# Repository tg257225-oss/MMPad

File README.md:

# MMPad
This is my first macro pad. Its a simple 3x3 grid of switches, with a rotary encoder and OLED display (which will likely be Jolteon). This project was really fun (and frustrating) to make, but I did learn a lot and hope to make an even better one in the future!
# PCB/Schematic
The PCB and Schematic were designed in Kicad.

# CAD
The case and plate were designed in Fusion360. 

## BOM
- 1x 0.96" OLED Screen - $3.90 on SeeedStudio
- 1x EC11 Rotary Encoder - $1.99 on Keebio
- 9x MX Switches - $0.99 on AliExpress (10-count Cherry MX Brown Switches)
- 10x 1N4148 Diodes - $2.99 on Keebio 
- 1x Seeed XIAO RP2040 $3.99 on SeeedStudio
- 9x DSA Keycaps - $0.99 on AliExpress (10-count DSA 1U Black Keycaps)
- 4x M3x16mm screws - $8.99 on Amazon
### Total is $23.84

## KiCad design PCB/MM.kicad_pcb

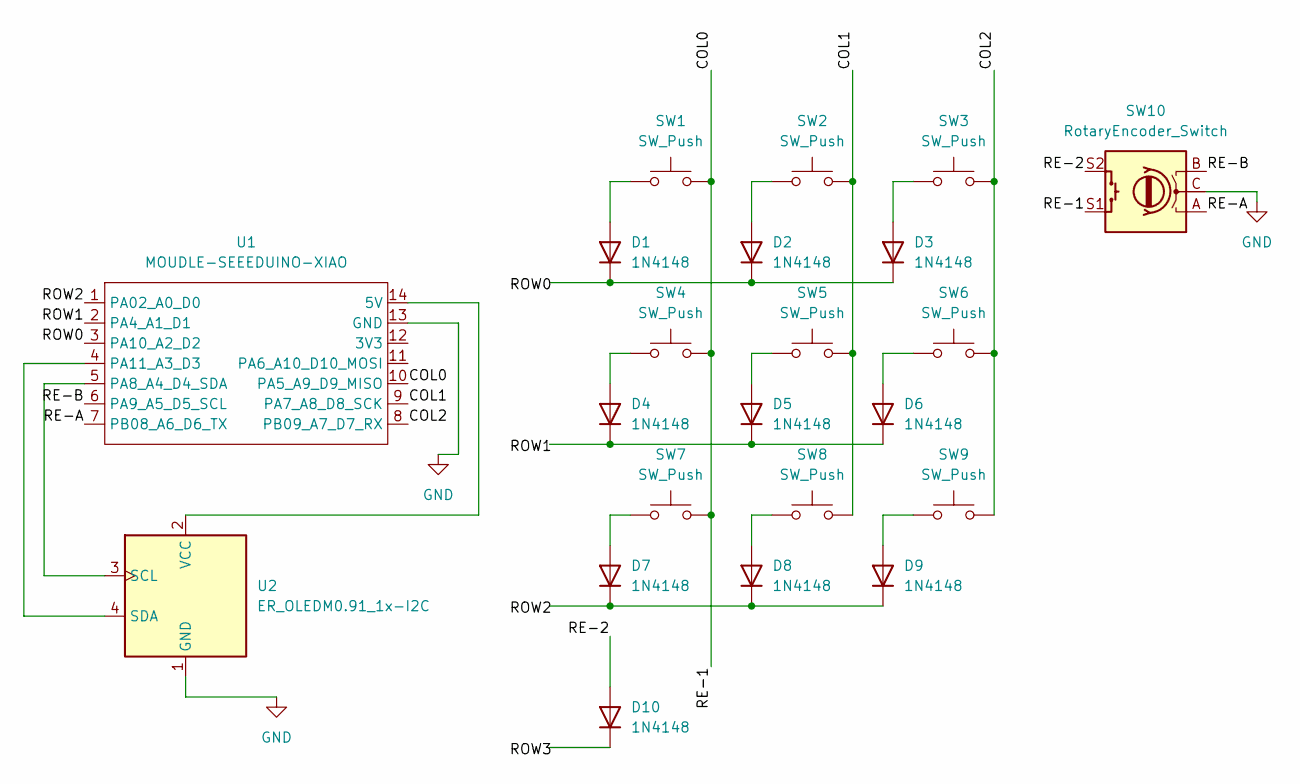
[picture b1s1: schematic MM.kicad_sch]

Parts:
D1, D2, D3, D4, D5, D6, D7, D8, D9, D10: 1N4148; D_DO-35_SOD27_P7.62mm_Horizontal
SW1, SW2, SW3, SW4, SW5, SW6, SW7, SW8, SW9: SW_Push; SW_Cherry_MX_1.00u_PCB
SW10: RotaryEncoder_Switch; RotaryEncoder_Alps_EC11E-Switch_Vertical_H20mm
U1: MOUDLE-SEEEDUINO-XIAO; XIAO-Generic-Hybrid-14P-2.54-21X17.8MM
U2: ER_OLEDM0.91_1x-I2C

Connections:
/COL0: SW1.2, SW4.2, SW7.2, SW10.S1, U1.10 (PA5_A9_D9_MISO)
/COL1: SW2.2, SW5.2, SW8.2, U1.9 (PA7_A8_D8_SCK)
/COL2: SW3.2, SW6.2, SW9.2, U1.8 (PB09_A7_D7_RX)
/RE-2: D10.2 (A_2), SW10.S2
/RE-A: SW10.A, U1.7 (PB08_A6_D6_TX)
/RE-B: SW10.B, U1.6 (PA9_A5_D5_SCL)
/ROW0: U1.3 (PA10_A2_D2)
/ROW1: U1.2 (PA4_A1_D1)
/ROW2: U1.1 (PA02_A0_D0)
GND: SW10.C, U1.13 (GND), U2.1 (GND)
unnamed: D1.2 (A), SW1.1
unnamed: D1.1 (K), D2.1 (K), D3.1 (K)
unnamed: D2.2 (A), SW2.1
unnamed: D3.2 (A), SW3.1
unnamed: D4.2 (A), SW4.1
unnamed: D4.1 (K), D5.1 (K), D6.1 (K)
unnamed: D5.2 (A), SW5.1
unnamed: D6.2 (A), SW6.1
unnamed: D7.2 (A), SW7.1
unnamed: D7.1 (K), D8.1 (K), D9.1 (K)
unnamed: D8.2 (A), SW8.1
unnamed: D9.2 (A), SW9.1
unnamed: U1.14 (5V), U2.2 (VCC)
unnamed: U1.5 (PA8_A4_D4_SDA), U2.3 (SCL)
unnamed: U1.4 (PA11_A3_D3), U2.4 (SDA)

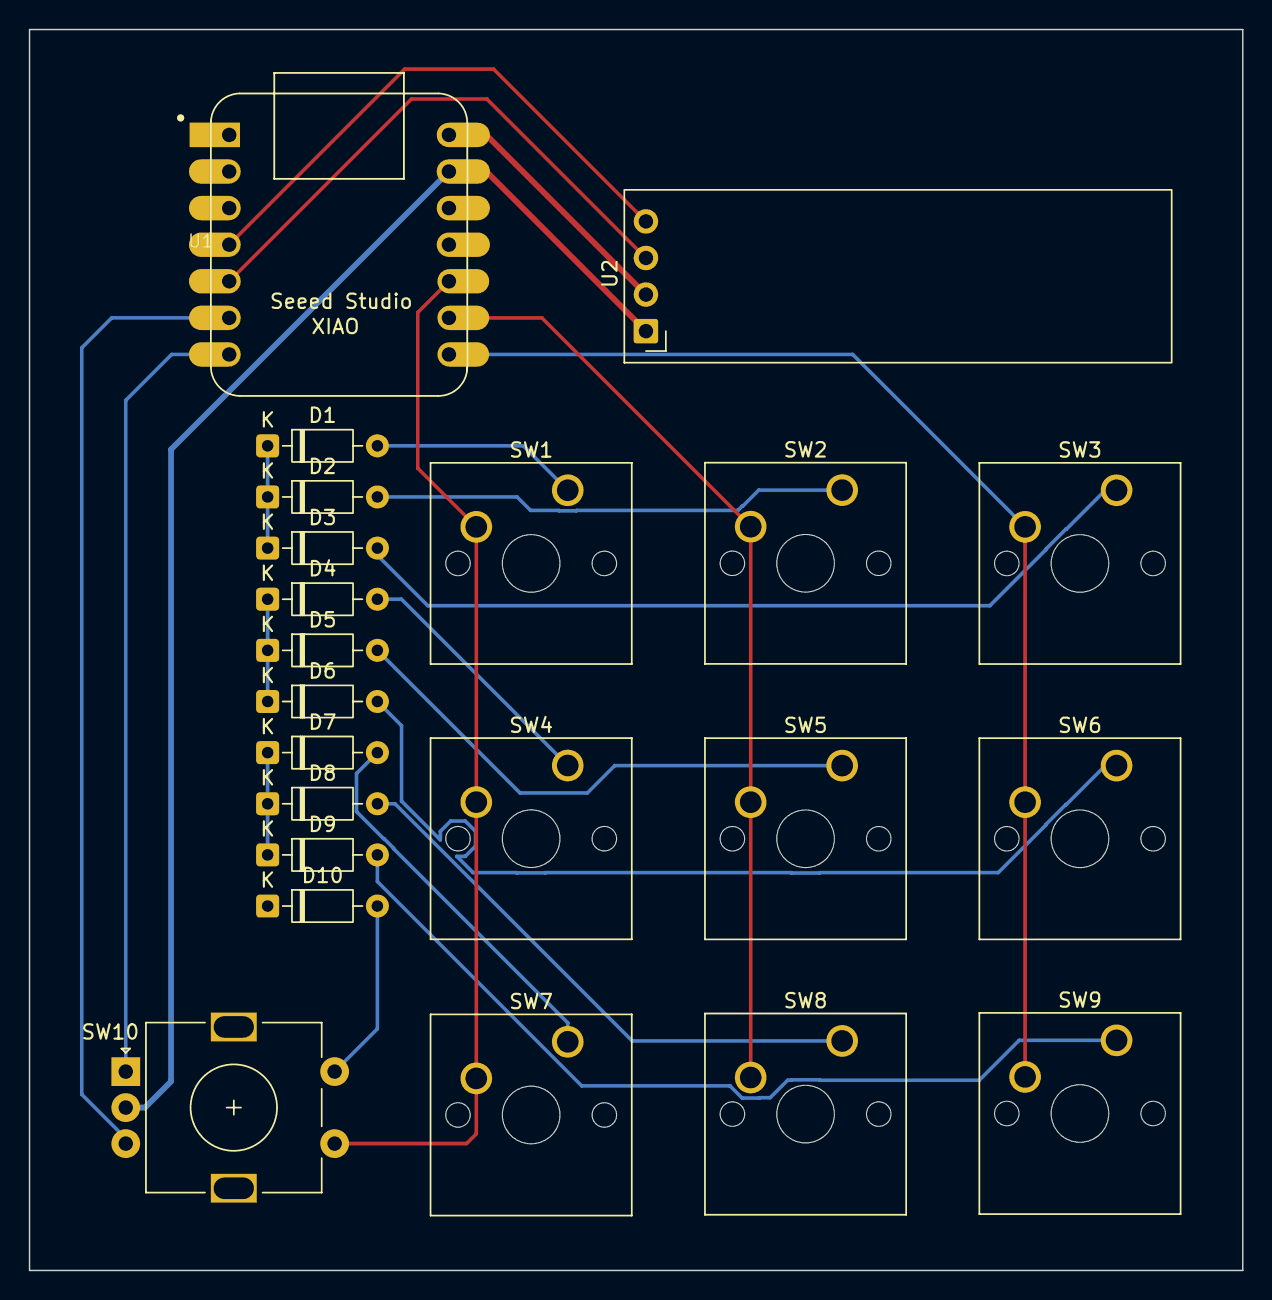
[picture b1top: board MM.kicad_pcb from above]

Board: 2 copper layers, 84.2 x 86.1 mm, 22 parts (0 on the bottom side), 22 nets.

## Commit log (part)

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2026-06-10 Create assets
2026-06-10 Enhance README with project details and features
    Added project description and features to README.
2026-06-10 Update features section formatting in README
2026-06-10 Change PCB/Schematic header to second-level heading
2026-06-11 Revise README with project overview and BOM
    Updated project description and added BOM details.
2026-06-11 Add images section with CAD screenshot
2026-06-11 Fix image path in README.md
2026-06-11 Add schematic and PCB images to README
2026-06-11 Add screenshot of plate and case separated
2026-06-11 Rename plate and case.png to plateandcase.png
2026-06-11 Fix image filename for plate and case screenshot
2026-06-27 Update README for clarity and remove 'most likely'
2026-06-27 Fix typo in BOM section of README
2026-06-27 Revise BOM with pricing details
    Updated BOM with prices and removed unnecessary lines.
2026-06-27 Fix formatting of M3x16mm screws entry in README
2026-06-27 Enhance README with PCB and Schematic details
    Added PCB and Schematic section with images to README.
2026-06-27 Add CAD section to README with design images
    Added CAD section with images of the design.
